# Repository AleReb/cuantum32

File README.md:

# Sistema de Análisis de Opiniones Distribuido I2C

## Changelog / Recent Updates (Quantum32 V3)
- **2025-12-22**:
  - **Fixed Blocking**: Master V3 now updates the OLED display continuously, even during high-speed Python batched sampling.
  - **Fixed Slave LED**: Slaves now explicitly use **Pin 7** for the status LED and give visual feedback on every I2C RX/TX event.
  - **Environment**: Fixed local Python environment initialization.

Sistema distribuido basado en Arduino que utiliza comunicación I2C para coordinar múltiples dispositivos esclavos que realizan análisis de opiniones (a favor/en contra/neutral). El maestro agrega los resultados y los muestra en una pantalla OLED con marcas de tiempo del RTC.

## 📋 Descripción

Este proyecto implementa una **simulación pedagógica de holografía (Toy Holography)** inspirada en el principio holográfico y la correspondencia AdS/CFT. Utiliza una arquitectura maestro-esclavo donde:

- **Maestro (Bulk)**: Representa el volumen ("bulk") del espacio-tiempo. Reconstruye información lógica a partir de las correlaciones de los esclavos, monitorea el ambiente y visualiza la "reconstrucción holográfica".
- **Esclavos (Boundary)**: Representan el borde ("boundary") del sistema. Generan observables locales con ruido y pérdida simulada que el maestro utiliza para inferir el estado del volumen.

El sistema ilustra cómo propiedades, corrección de errores y geometrías emergentes pueden surgir de interacciones distribuidas simples sobre un bus I2C.

## 🔧 Hardware Requerido

### Maestro (Master)
- 1x ESP32-S3 Super Mini (o compatible)
- 1x Pantalla OLED 1.3" (SH1106, dirección I2C 0x3C)
- 1x Módulo RTC DS3231 (dirección I2C 0x68)
- 1x Sensor BME280 (Temp/Hum/Pres, dirección I2C 0x76)
- 1x Módulo MicroSD (SPI: CS=7, MOSI=6, MISO=5, SCLK=4)
- 1x LED RGB (NeoPixel/WS2812B en pin 48)
- Resistencias pull-up 4.7kΩ (2x para SDA y SCL)

### Cada Esclavo (Slave)
- 1x Arduino (Uno, Nano, ESP32, etc.)
- Conexión al bus I2C compartido

### Adicional
- Cables jumper
- Fuente de alimentación adecuada (si se usan múltiples dispositivos)
- Protoboard o PCB para conexiones

### 2. Configurar el Maestro
1. Abrir `master.ino` en Arduino IDE
2. Revisar `config.h` para ajustar configuraciones si es necesario (pines, direcciones, habilitar/deshabilitar módulos)
3. Conectar el Arduino maestro
4. Seleccionar placa y puerto correcto
5. Cargar el código

### 3. Configurar los Esclavos
Para **cada esclavo**:
1. Abrir `slave.ino` en Arduino IDE
2. **IMPORTANTE**: Cambiar la dirección I2C única:
   ```cpp
   #define SLAVE_ADDRESS 0x10  // Cambiar a 0x11, 0x12, 0x13, etc.
   ```
3. Conectar el Arduino esclavo
4. Cargar el código
5. Repetir para cada esclavo adicional

### 4. Conexiones de Hardware
Ver [WIRING.md](WIRING.md) para diagramas detallados de conexión.

**Conexiones básicas I2C:**
- Conectar **SDA** de todos los dispositivos juntos
- Conectar **SCL** de todos los dispositivos juntos
- Conectar **GND** común
- Agregar resistencias pull-up de 4.7kΩ en SDA y SCL al voltaje de alimentación (3.3V o 5V según dispositivos)

## ⚙️ Configuración Avanzada

### Agregar Más Esclavos
1. Editar `config.h` en el maestro:
   ```cpp
   const uint8_t SLAVE_ADDRESSES[] = {
     SLAVE_ADDR_1,
     SLAVE_ADDR_2,
     SLAVE_ADDR_3,
     SLAVE_ADDR_4,
     0x14,  // Nuevo esclavo 5
     0x15   // Nuevo esclavo 6
   };
   ```
2. Programar nuevos esclavos con direcciones únicas
3. Conectar al bus I2C

### Habilitar/Deshabilitar Módulos
En `config.h` puedes activar o desactivar componentes:
```cpp
#define ENABLE_OLED       true   // Pantalla OLED
#define ENABLE_RTC        true   // Reloj RTC
#define ENABLE_SD_LOGGING true   // Registro en SD
#define ENABLE_BME280     true   // Sensor ambiental
#define ENABLE_RGB_LED    true   // LED de estado
```

### Ajustar Velocidad I2C
En `config.h`:
```cpp
#define I2C_CLOCK_SPEED 100000  // 100 kHz (estándar) o 400000 (rápido)
```

## 📊 Uso

### Monitor Serial
Abrir el monitor serial (115200 baud) para ver:
- Escaneo de dispositivos I2C al inicio
- Resultados agregados en tiempo real
- Confirmación de escritura en SD (`>> Data saved to SD`)
- Mensajes de error o advertencias

### Pantalla OLED (MasterV2)
La pantalla ahora visualiza la dinámica de la simulación en tiempo real:
- **Header**: `T:####` (Contador de Ticks de simulación).
- **Status Row**: Estado de cada esclavo (Cuadro lleno = OK, Vacío = Missing).
- **Bulk Reconstruction**: Barra de progreso que muestra qué porcentaje de la lógica del "bulk" ha sido recuperada exitosamente desde el borde.
  - El porcentaje se muestra centrado con contraste dinámico para evitar solapamiento.
- **Boundary Map (2x2)**: Visualización matricial del ruido en cada esclavo (cuadros más llenos = menos ruido/mejor señal).
- **History Graph**: Un gráfico histórico a la derecha que muestra la evolución de la `Reconstruction Ratio` en los últimos 40 ticks.
- **Footer**: Máscaras de bits (Boundary/Bulk) y datos ambientales.

### Registro en Tarjeta SD
El sistema registra en `datalog.csv`:
`timestamp, tick, active_slaves, boundary_mask, bulk_mask, recon_ratio, loss_sum, noise_avg, temp, hum`

### Disclaimer de "Veracidad Científica"
> [!IMPORTANT]
> **Nota sobre la precisión científica**:
> Este código es un **"modelo de juguete" (toy model)** con fines educativos y de prototipado.
> *   **No es** una simulación cuántica real (no hay entrelazamiento cuántico real ni hamiltonianos complejos).
> *   La "Reconstrucción del Bulk" usa una lógica de máscaras de bits simplificada para *ilustrar* conceptos de corrección de errores cuánticos, pero no implementa un código corrección de errores (QECC) riguroso como el código de HaPPY o Shor.
> *   Su objetivo es proveer una intuición física de cómo información local en el borde puede redundar en información robusta en el volumen, usando hardware clásico accesible.

## 🔍 Solución de Problemas

### No se detectan dispositivos I2C
- Verificar conexiones SDA/SCL
- Confirmar resistencias pull-up instaladas (4.7kΩ)
- Revisar alimentación de todos los dispositivos
- Usar sketch de escaneo I2C para detectar dispositivos

### OLED no muestra nada
- Verificar dirección I2C (0x3C o 0x3D)
- Confirmar librería correcta (SH1106 vs SSD1306)
- Revisar conexiones y alimentación

### Esclavos no responden
- Verificar direcciones únicas para cada esclavo
- Confirmar que los esclavos están alimentados
- Revisar que el código del esclavo se cargó correctamente
- Verificar timeout en `config.h` (aumentar si es necesario)

### Error en SD Card
- Verificar conexiones SPI (CS, MOSI, MISO, SCLK)
- Asegurar que la tarjeta está formateada en FAT32
- Revisar si el archivo `datalog.csv` está abierto en otro lugar

## 🛠️ Desarrollo Futuro

Posibles mejoras:
- [ ] Implementar checksums para validación de datos
- [ ] Agregar comandos de configuración desde el maestro
- [ ] Interfaz web para visualización remota
- [ ] Modo de bajo consumo para operación con batería
- [*] Implementar cuantum life! revisa la carpeta cuantum_life para ver el código del juego de la vida. 

## 👤 Autor

**Alejandro Rebolledo**  
Email: arebolledo@udd.cl  
Fecha: 2025-12-01  

**Atribución Original**
El código original fue creado por **Vicente Lorca** [@vlorcap](https://github.com/vlorcap) ; este proyecto es un derivado y el concepto inicial proviene de Vicente.

## 📄 Licencia

Este proyecto está licenciado bajo **Creative Commons Attribution-NonCommercial 4.0 International (CC BY-NC 4.0)**.

Ver el archivo [LICENSE](LICENSE) para más detalles.

### Descargo de Responsabilidad

Este código se proporciona "tal cual", sin garantías de ningún tipo, expresas o implícitas. El autor no se hace responsable de ningún daño o pérdida que pueda resultar del uso de este código. Úselo bajo su propio riesgo.

## 🤝 Contribuciones

Las contribuciones son bienvenidas. Por favor:
1. Fork el proyecto
2. Crea una rama para tu feature (`git checkout -b feature/AmazingFeature`)
3. Commit tus cambios (`git commit -m 'Add some AmazingFeature'`)
4. Push a la rama (`git push origin feature/AmazingFeature`)
5. Abre un Pull Request

## 📞 Soporte

Para preguntas o problemas, por favor abre un issue en el repositorio de GitHub.

---

**¡Gracias por usar este proyecto!** ⭐ Si te resulta útil, considera darle una estrella al repositorio.

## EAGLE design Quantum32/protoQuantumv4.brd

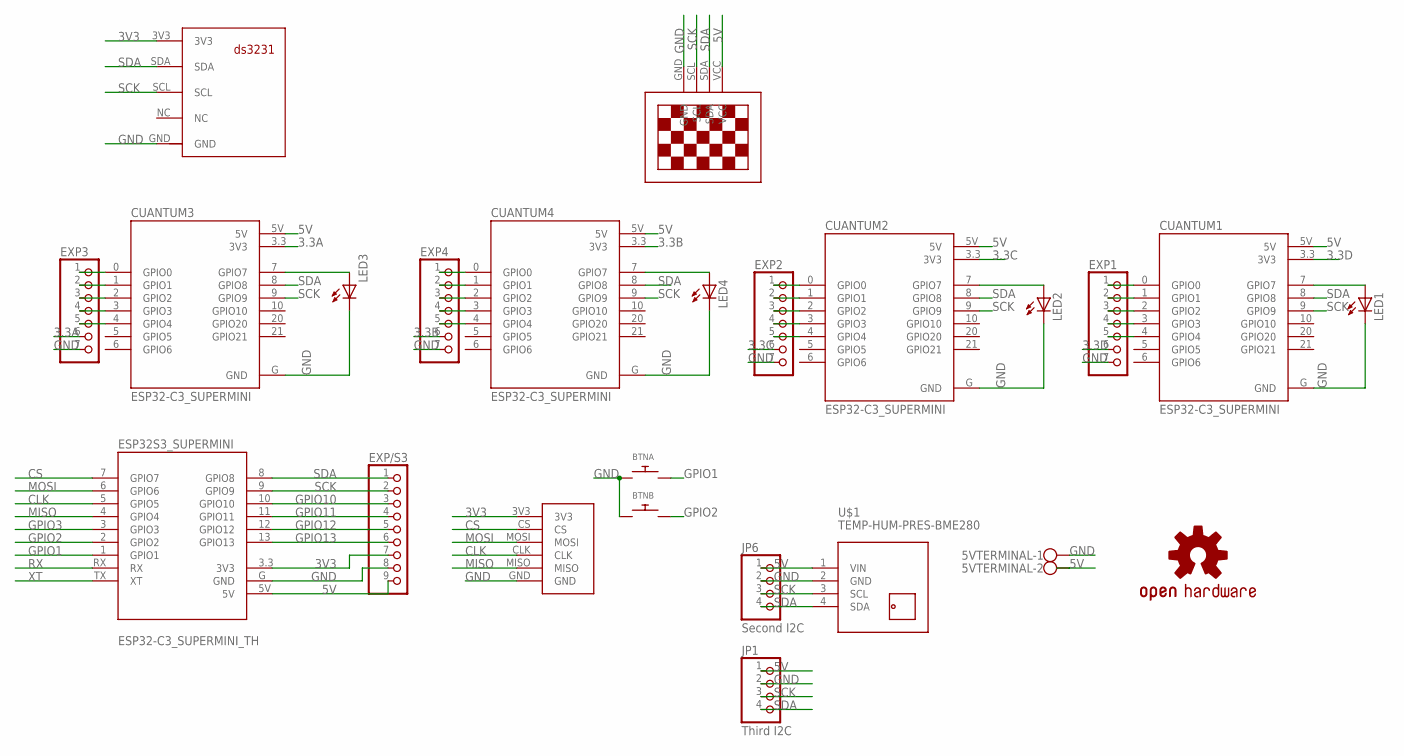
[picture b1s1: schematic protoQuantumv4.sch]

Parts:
5VTERMINAL: W237-102
BTNA: SWITCH_PUSHBUTTONEVQ-PE; TACT_PANA-EVQ
BTNB: SWITCH_PUSHBUTTONEVQ-PE; TACT_PANA-EVQ
CUANTUM1, CUANTUM2, CUANTUM3, CUANTUM4: ESP32-C3_SUPERMINI; MODULE_ESP32-C3_SUPERMINI_TH
ESP32S3_SUPERMINI: ESP32-C3_SUPERMINI_TH; MODULE_ESP32-C3_SUPERMINI_TH
EXP1, EXP2, EXP3, EXP4: PINHD-1X7; 1X07
EXP/S3: PINHD-1X9; 1X09
JP1: Third I2C; 1X04
JP6: Second I2C; 1X04
LED1, LED2, LED3, LED4: LED3MM
LOGO1: OSHW-LOGOM; OSHW-LOGO-M
OLED1.3: 13"OLED13"OLED; 1.3"OLED
U$1: TEMP-HUM-PRES-BME280
U$2: SD_KUSKALLA
U$4: RTC; RTCDS3231FP

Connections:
3.3A: CUANTUM3.3.3 (3V3), EXP3.6
3.3B: CUANTUM4.3.3 (3V3), EXP4.6
3.3C: CUANTUM2.3.3 (3V3), EXP2.6
3.3D: CUANTUM1.3.3 (3V3), EXP1.6
3V3: ESP32S3_SUPERMINI.3.3 (3V3), EXP/S3.7, U$2.3V3, U$4.3V3
5V: 5VTERMINAL.2, CUANTUM1.5V, CUANTUM2.5V, CUANTUM3.5V, CUANTUM4.5V, ESP32S3_SUPERMINI.5V, EXP/S3.9, JP1.1, JP6.1, OLED1.3.VCC, U$1.1 (VIN)
CLK: ESP32S3_SUPERMINI.5 (GPIO5), U$2.CLK
CS: ESP32S3_SUPERMINI.7 (GPIO7), U$2.CS
GND: 5VTERMINAL.1, BTNA.P$1, BTNB.P$1, CUANTUM1.G (GND), CUANTUM2.G (GND), CUANTUM3.G (GND), CUANTUM4.G (GND), ESP32S3_SUPERMINI.G (GND), EXP1.7, EXP2.7, EXP3.7, EXP4.7, EXP/S3.8, JP1.2, JP6.2, LED1.K (C), LED2.K (C), LED3.K (C), LED4.K (C), OLED1.3.GND, U$1.2 (GND), U$2.GND, U$4.GND
GPIO1: BTNA.P$2, ESP32S3_SUPERMINI.1 (GPIO1)
GPIO2: BTNB.P$2, ESP32S3_SUPERMINI.2 (GPIO2)
GPIO3: ESP32S3_SUPERMINI.3 (GPIO3)
GPIO10: ESP32S3_SUPERMINI.10 (GPIO10), EXP/S3.3
GPIO11: ESP32S3_SUPERMINI.11 (GPIO11), EXP/S3.4
GPIO12: ESP32S3_SUPERMINI.12 (GPIO12), EXP/S3.5
GPIO13: ESP32S3_SUPERMINI.13 (GPIO13), EXP/S3.6
MISO: ESP32S3_SUPERMINI.4 (GPIO4), U$2.MISO
MOSI: ESP32S3_SUPERMINI.6 (GPIO6), U$2.MOSI
unnamed: CUANTUM4.7 (GPIO7), LED4.A
unnamed: CUANTUM4.0 (GPIO0), EXP4.1
unnamed: CUANTUM3.7 (GPIO7), LED3.A
unnamed: CUANTUM1.0 (GPIO0), EXP1.1
unnamed: CUANTUM1.1 (GPIO1), EXP1.2
unnamed: CUANTUM2.7 (GPIO7), LED2.A
unnamed: CUANTUM1.7 (GPIO7), LED1.A
unnamed: CUANTUM3.0 (GPIO0), EXP3.1
unnamed: CUANTUM3.1 (GPIO1), EXP3.2
unnamed: CUANTUM3.2 (GPIO2), EXP3.3
unnamed: CUANTUM3.3 (GPIO3), EXP3.4
unnamed: CUANTUM3.4 (GPIO4), EXP3.5
unnamed: CUANTUM4.1 (GPIO1), EXP4.2
unnamed: CUANTUM4.2 (GPIO2), EXP4.3
unnamed: CUANTUM4.3 (GPIO3), EXP4.4
unnamed: CUANTUM4.4 (GPIO4), EXP4.5
unnamed: CUANTUM2.0 (GPIO0), EXP2.1
unnamed: CUANTUM2.1 (GPIO1), EXP2.2
unnamed: CUANTUM2.2 (GPIO2), EXP2.3
unnamed: CUANTUM2.3 (GPIO3), EXP2.4
unnamed: CUANTUM2.4 (GPIO4), EXP2.5
unnamed: CUANTUM1.2 (GPIO2), EXP1.3
unnamed: CUANTUM1.3 (GPIO3), EXP1.4
unnamed: CUANTUM1.4 (GPIO4), EXP1.5
RX: ESP32S3_SUPERMINI.RX
SCK: CUANTUM1.9 (GPIO9), CUANTUM2.9 (GPIO9), CUANTUM3.9 (GPIO9), CUANTUM4.9 (GPIO9), ESP32S3_SUPERMINI.9 (GPIO9), EXP/S3.2, JP1.3, JP6.3, OLED1.3.SCL, U$1.3 (SCL), U$4.SCL
SDA: CUANTUM1.8 (GPIO8), CUANTUM2.8 (GPIO8), CUANTUM3.8 (GPIO8), CUANTUM4.8 (GPIO8), ESP32S3_SUPERMINI.8 (GPIO8), EXP/S3.1, JP1.4, JP6.4, OLED1.3.SDA, U$1.4 (SDA), U$4.SDA
XT: ESP32S3_SUPERMINI.TX (XT)

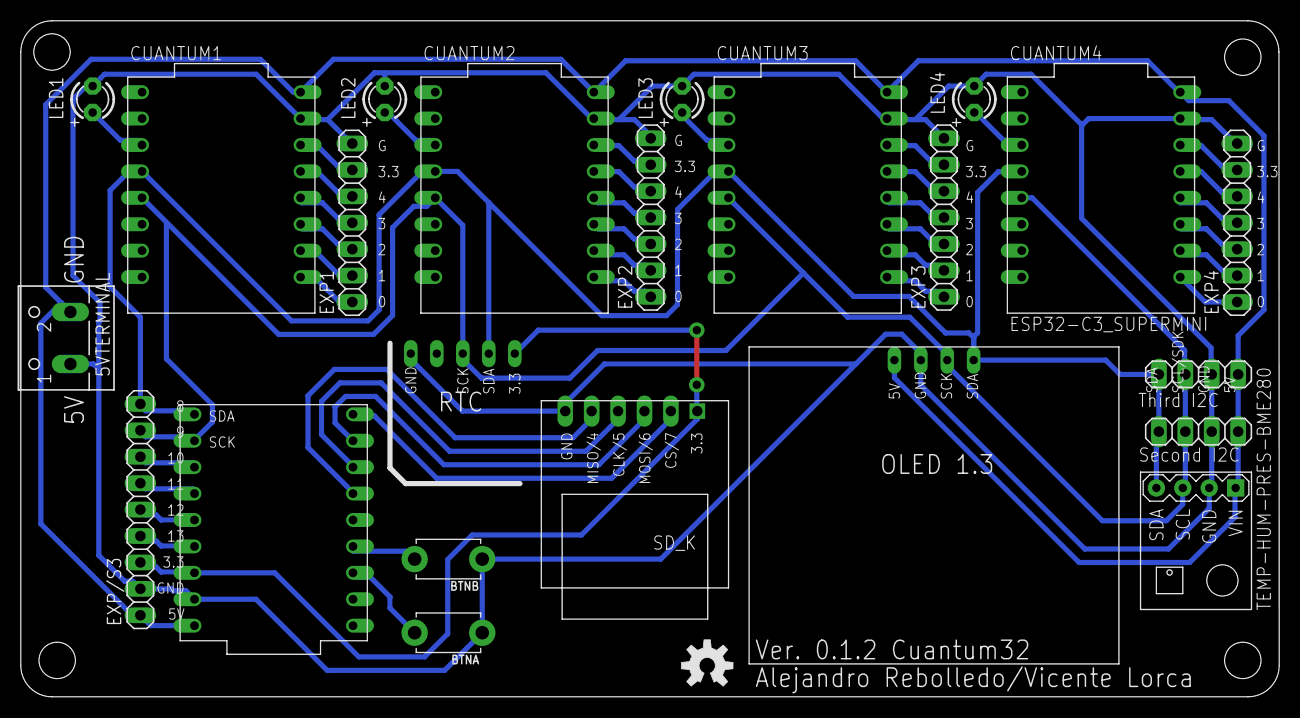
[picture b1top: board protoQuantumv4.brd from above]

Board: 2 copper layers, 121.0 x 65.0 mm, 24 parts (0 on the bottom side), 43 nets.

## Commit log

2025-12-01 feat: Document new master features including BME280, SD logging, RGB LED, and ESP32-S3.
2025-12-02 feat: Implement initial I2C Master Opinion Analysis System with OLED, RTC, RGB LED, SD logging, and BME280 integration. add users buttons 1 and 2 to gnd input_pullup
2025-12-16 Add holographic simulation guidance
2025-12-16 feat: introduce non-blocking master and slave nodes for Toy Holography system.
2025-12-19 feat: implement Cuantum Life, a holographic Game of Life with master/slave firmware and conceptual documentation.
2025-12-22 feat: Initialize project environment with core dependencies and add MaxCut client script.
2025-12-23 se agrega una version de pc_client_maxcutV2 y una explcacion de la nueva version
2025-12-23 feat: Implement Cuantum Life V2.3.1, featuring independent I2C tick, non-blocking I2C/buttons, robust retries, and health reporting.
2025-12-29 feat: Add initial web portal for Quantum32 Hybrid Sampler with serial communication, data processing, and visualization.

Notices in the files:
parts and their libraries:
diy-modules: Released under the Creative Commons Attribution 4.0 International License: http://creativecommons.org/licenses/by/4.0
SparkFun-Aesthetics: Licensing: Creative Commons ShareAlike 4.0 International - https://creativecommons.org/licenses/by-sa/4.0
